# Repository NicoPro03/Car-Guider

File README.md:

# Car-Guider
Proyect--- Car controller with hands.

---Campusano Nicolas----
---Benitez Gabriel------
---Benitez Bruno--------

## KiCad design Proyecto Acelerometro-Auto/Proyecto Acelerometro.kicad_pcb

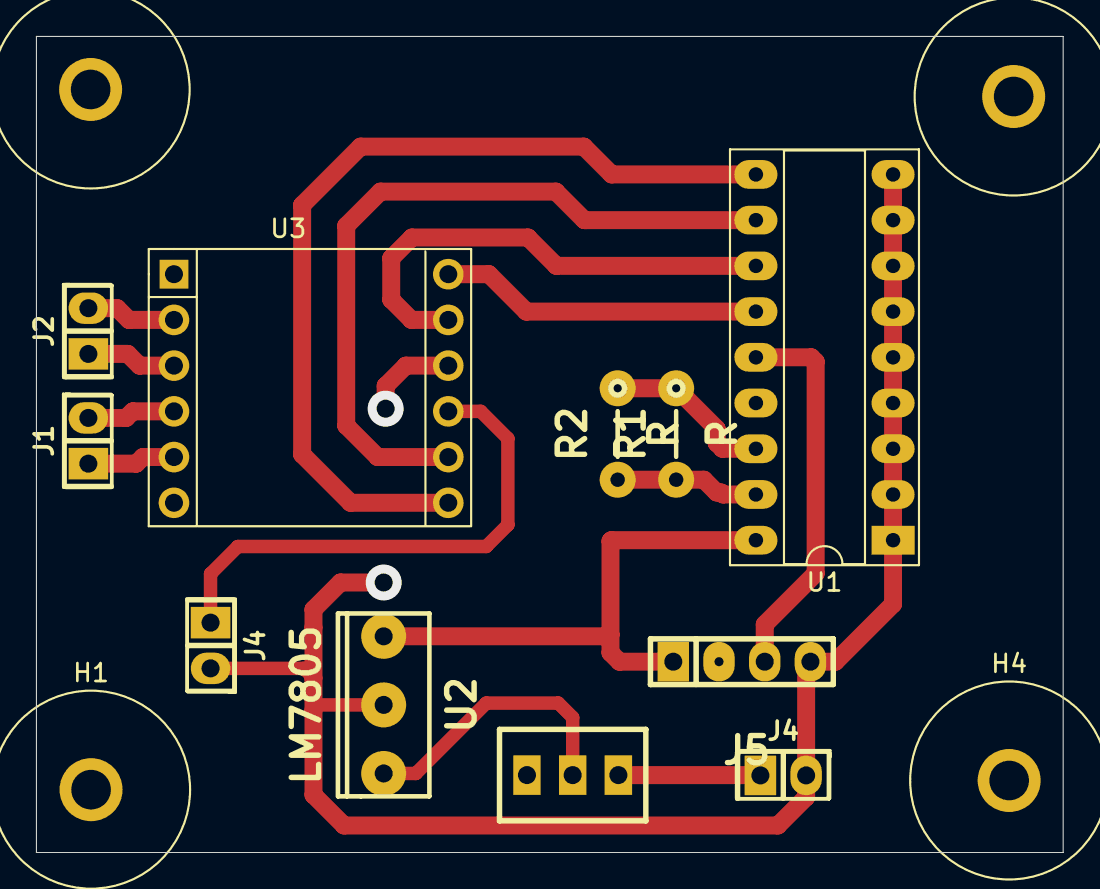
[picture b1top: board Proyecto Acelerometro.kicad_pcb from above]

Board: 2 copper layers, 57.0 x 45.3 mm, 15 parts (0 on the bottom side), 15 nets.

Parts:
H1, H2, H3, H4: MountingHole_Pad; Banana_Jack_1Pin
J1, J2: MOTOR; Pin_Header_2
J4, J4#2: BATERIA; Pin_Header_2
J5: RF-5V; pin_strip_4
R1, R2: R; RES0.2
SWITCH1: SW_Push; SW_SPDT_TH_100Mils_VERTICAL
U1: HT12D; DIP-18_300_socket
U2: LM7805; to220
U3: Drv8833; DRV8833

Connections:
/DATA: J5.3, U1.14
/GND: J4.2, J4#2.2, J5.4, U1.1, U1.2, U1.3, U1.4, U1.5, U1.6, U1.7, U1.8, U1.9, U2.2, U3.10 (GND)
/IN1: U1.10, U3.7 (IN1)
/IN2: U1.11, U3.8 (IN2)
/IN3: U1.12, U3.11 (IN3)
/IN4: U1.13, U3.12 (IN4)
/OUT1: J2.2, U3.1 (OUT1)
/OUT2: J2.1, U3.3 (OUT2)
/OUT3: J1.2, U3.4 (OUT3)
/OUT4: J1.1, U3.5 (OUT4)
/SW1: J4#2.1, SWITCH1.1
/SW2: SWITCH1.2, U2.1
/VCC: J4.1, J5.1, U1.18, U2.3, U3.9 (VCC)
unnamed: R1.1, R2.1, U1.16
unnamed: R1.2, R2.2, U1.17

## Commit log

2022-11-25 codigo del auto
2022-11-25 Informe
2022-11-25 SCH Y PCB
    Dentro de este archivo también se encuentra la huella del Driver8833
2022-11-25 SCH Y PCB
    archivos Kicad
2022-11-25 SCH Y PCB MANO
    Archivos Kicad Mano
